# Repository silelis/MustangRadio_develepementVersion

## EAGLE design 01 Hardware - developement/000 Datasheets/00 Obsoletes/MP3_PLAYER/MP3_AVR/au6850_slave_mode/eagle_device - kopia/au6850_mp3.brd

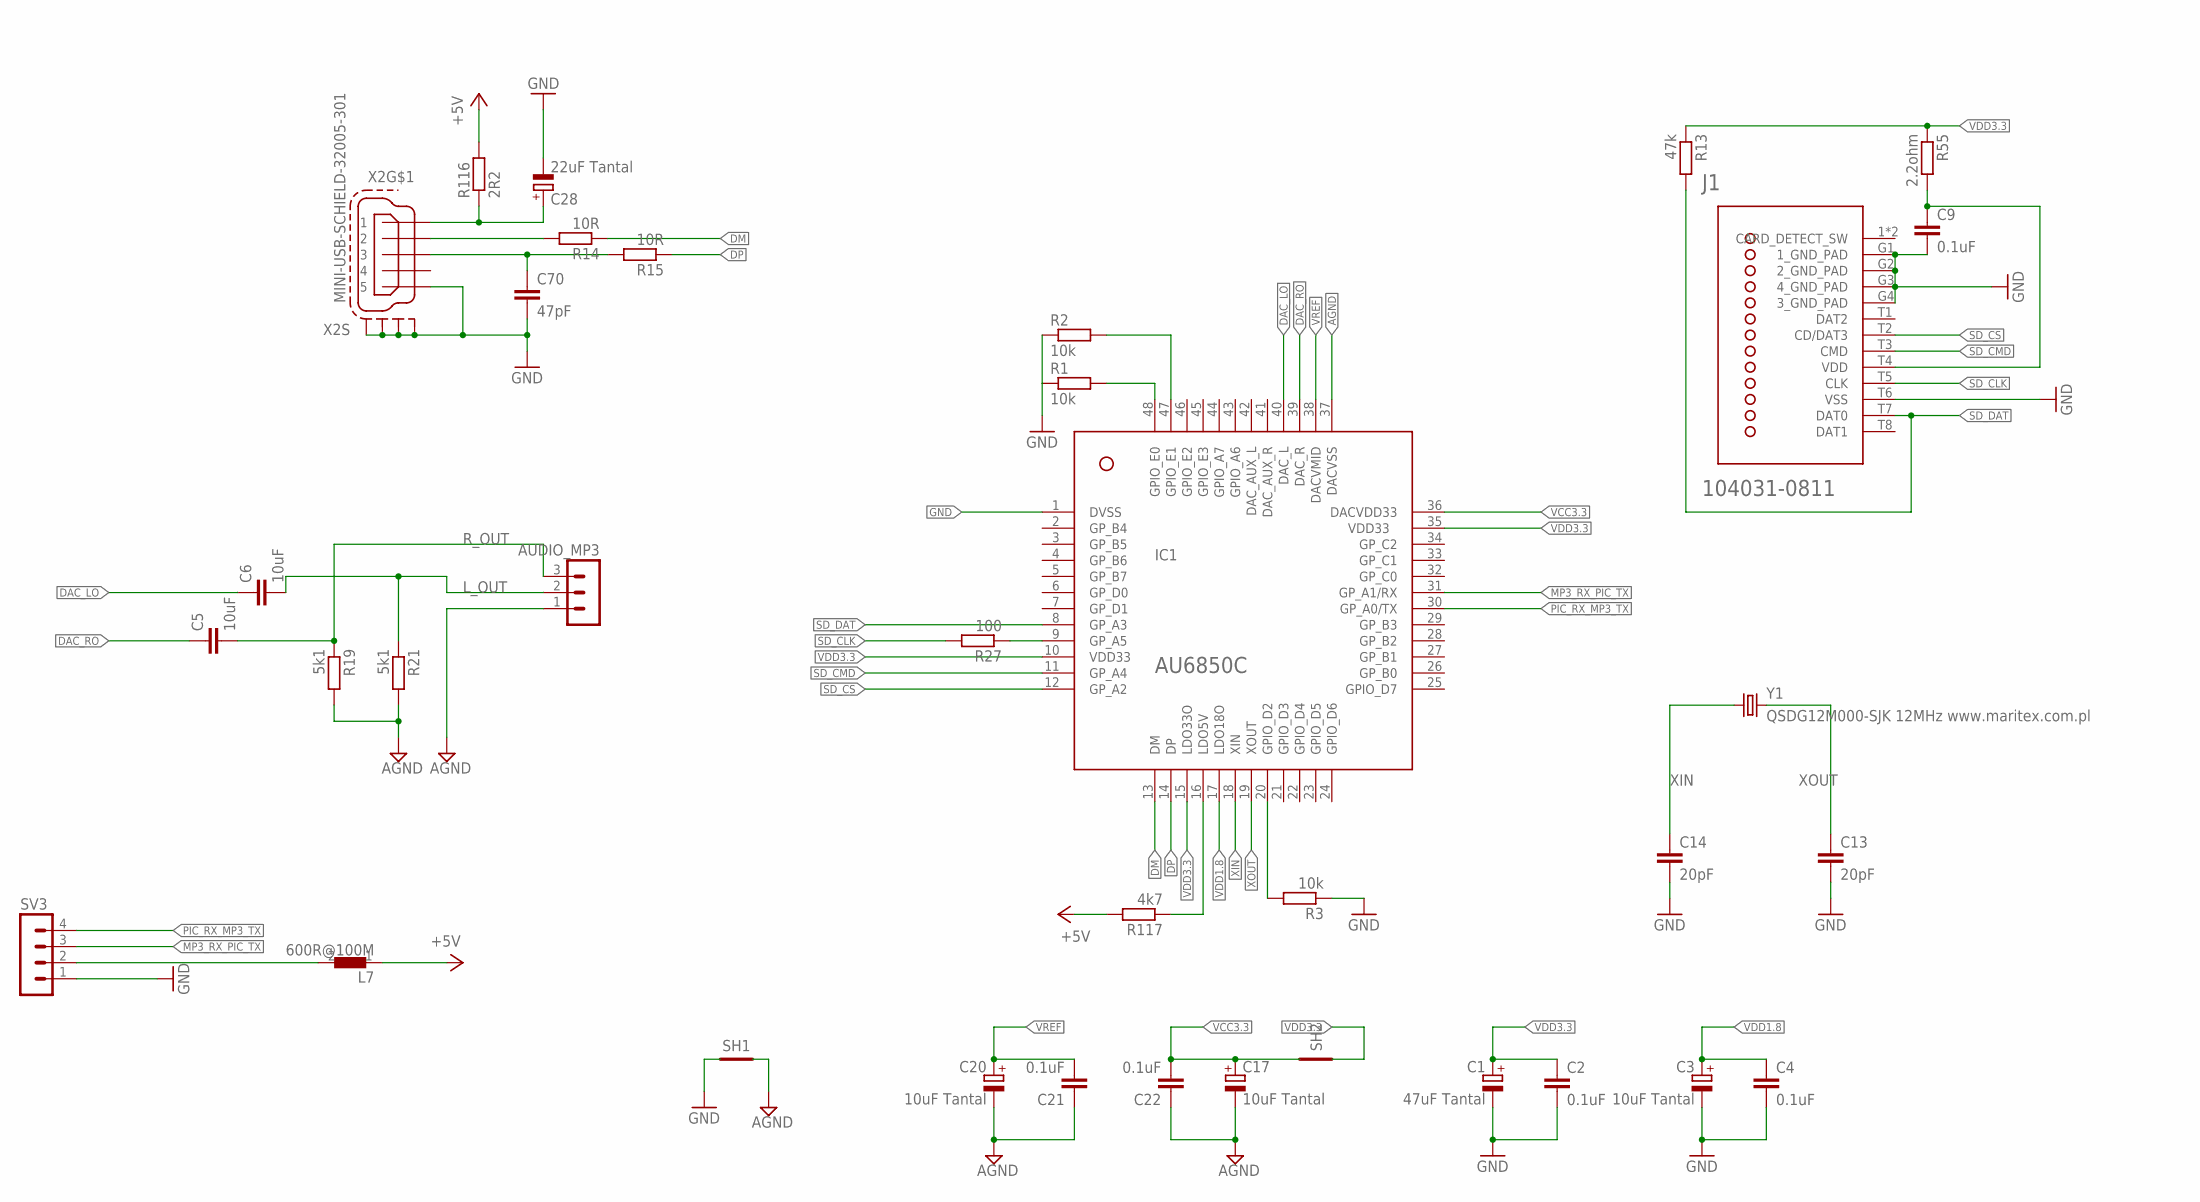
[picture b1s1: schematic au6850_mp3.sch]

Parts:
AUDIO_MP3: MA03-1
C1: 47uF Tantal; B/3528-21R
C2, C4, C9, C21, C22: 0.1uF; C0805
C3, C17, C20: 10uF Tantal; B/3528-21R
C5, C6: 10uF; C0805
C13, C14: 20pF; C0805
C28: 22uF Tantal; SMC_A
C70: 47pF; C0805
IC1: AU6850C; LQFP48-7X7
J1: MOLEX_104031-0811MOLEX_104031-0811_0_0; MOLEX_104031-0811_0
L7: 600R@100M; R0805
R1, R2, R3: 10k; R0805
R13: 47k; R0805
R14, R15: 10R; R0805
R19, R21: 5k1; R0805
R27: 100; R0805
R55: 2.2ohm; R0805
R116: 2R2; R0805
R117: 4k7; R0805
SH1: SHORT-HT5; SHORT_TOP-50
SH2: SHORT-V12_MILS; 12_MILS
SV3: MA04-1
X2: MINI-USB-SCHIELD-32005-301; 32005-301
Y1: QSDG12M000-SJK 12MHz www.maritex.com.pl; CRYSTAL-TXC-7A

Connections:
+5V: L7.1, R116.2, R117.2
AGND: AUDIO_MP3.1, C17.-, C20.-, C21.1, C22.1, IC1.37 (DACVSS), R19.2, R21.2, SH1.2
DAC_LO: C6.1, IC1.40 (DAC_L)
DAC_RO: C5.1, IC1.39 (DAC_R)
DM: IC1.13 (DM), R14.1
DP: IC1.14 (DP), R15.1
GND: C1.-, C2.2, C3.-, C4.2, C9.2, C13.2, C14.2, C28.-, C70.2, IC1.1 (DVSS), J1.G1 (1_GND_PAD), J1.G2 (2_GND_PAD), J1.G3 (4_GND_PAD), J1.G4 (3_GND_PAD), J1.T6 (VSS), R1.1, R2.1, R3.1, SH1.1, SV3.1, X2.5, X2.M1 (S1), X2.M2 (S2), X2.M3 (S3), X2.M4 (S4); also elsewhere on the board
L_OUT: AUDIO_MP3.2, C6.2, R21.1
MP3_RX_PIC_TX: IC1.31 (GP_A1/RX), SV3.3
unnamed: IC1.16 (LDO5V), R117.1
unnamed: IC1.9 (GP_A5), R27.1
unnamed: C28.+, R116.1, X2.1
unnamed: C70.1, R15.2, X2.3
unnamed: R14.2, X2.2
unnamed: L7.2, SV3.2
unnamed 16: C9.1, J1.T4 (VDD), R55.2; also elsewhere on the board
PIC_RX_MP3_TX: IC1.30 (GP_A0/TX), SV3.4
R_OUT: AUDIO_MP3.3, C5.2, R19.1
SD_CLK: J1.T5 (CLK), R27.2; also elsewhere on the board
SD_CMD: IC1.11 (GP_A4), J1.T3 (CMD); also elsewhere on the board
SD_CS: IC1.12 (GP_A2), J1.T2 (CD/DAT3); also elsewhere on the board
SD_DAT: IC1.8 (GP_A3), J1.T7 (DAT0), R13.2; also elsewhere on the board
SLAVE_D2: IC1.20 (GPIO_D2), R3.2
SLAVE_E0: IC1.48 (GPIO_E0), R1.2
SLAVE_E1: IC1.47 (GPIO_E1), R2.2
VCC3.3: C17.+, C22.2, IC1.36 (DACVDD33), SH2.P$2
VDD1.8: C3.+, C4.1, IC1.17 (LDO18O)
VDD3.3: C1.+, C2.1, IC1.10 (VDD33), IC1.15 (LDO33O), IC1.35 (VDD33), R13.1, R55.1, SH2.P$1
VREF: C20.+, C21.2, IC1.38 (DACVMID)
XIN: C14.1, IC1.18 (XIN), Y1.P$1 (1)
XOUT: C13.1, IC1.19 (XOUT), Y1.P$2 (2)

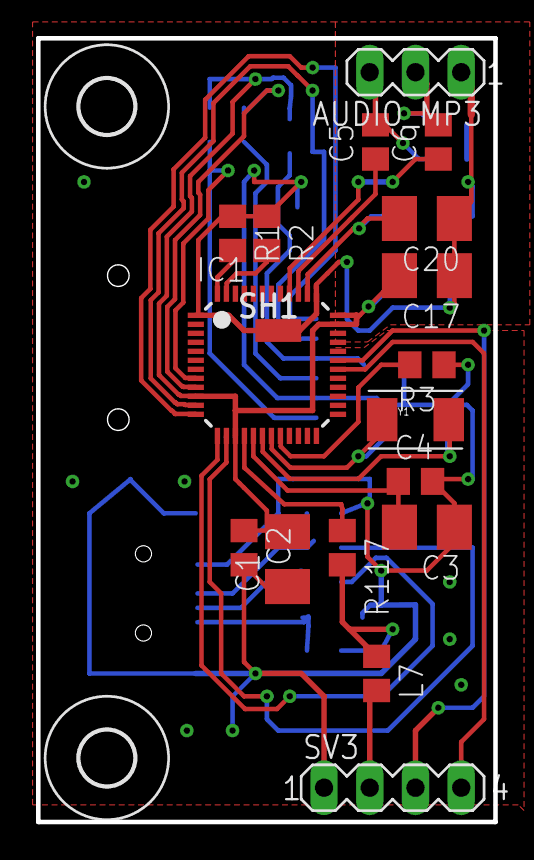
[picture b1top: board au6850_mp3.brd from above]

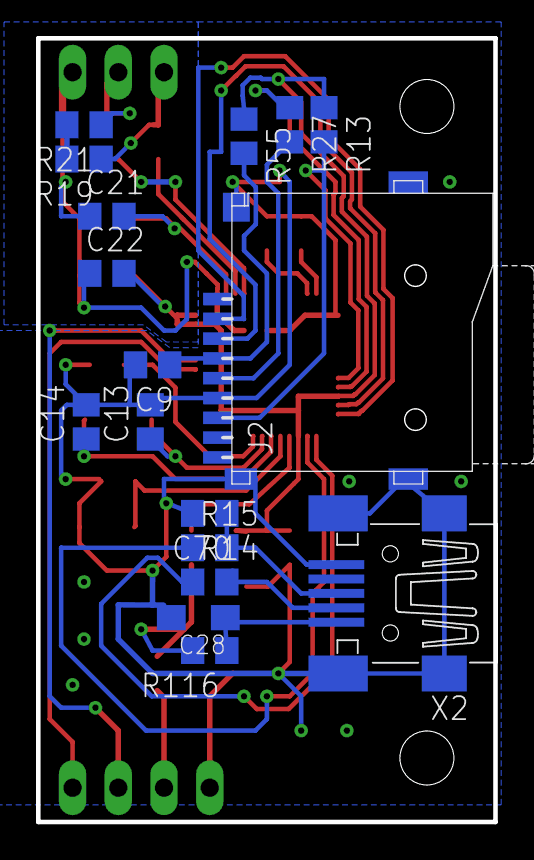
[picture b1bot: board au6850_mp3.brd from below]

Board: 2 copper layers, 25.4 x 43.5 mm, 38 parts (17 on the bottom side), 31 nets.

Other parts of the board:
J2: MICRO_SDMCSP-Q-08-A-SG-T/R; MICRO_SD_8PINS
U$1, U$2: 3,0

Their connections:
GND: J2.P$6, J2.P$SH_1, J2.P$SH_2, J2.P$SH_3, J2.P$SH_4; also elsewhere on the board
unnamed 16: J2.P$4; also elsewhere on the board
SD_CLK: J2.P$5; also elsewhere on the board
SD_CMD: J2.P$3; also elsewhere on the board
SD_CS: J2.P$2; also elsewhere on the board
SD_DAT: J2.P$7; also elsewhere on the board

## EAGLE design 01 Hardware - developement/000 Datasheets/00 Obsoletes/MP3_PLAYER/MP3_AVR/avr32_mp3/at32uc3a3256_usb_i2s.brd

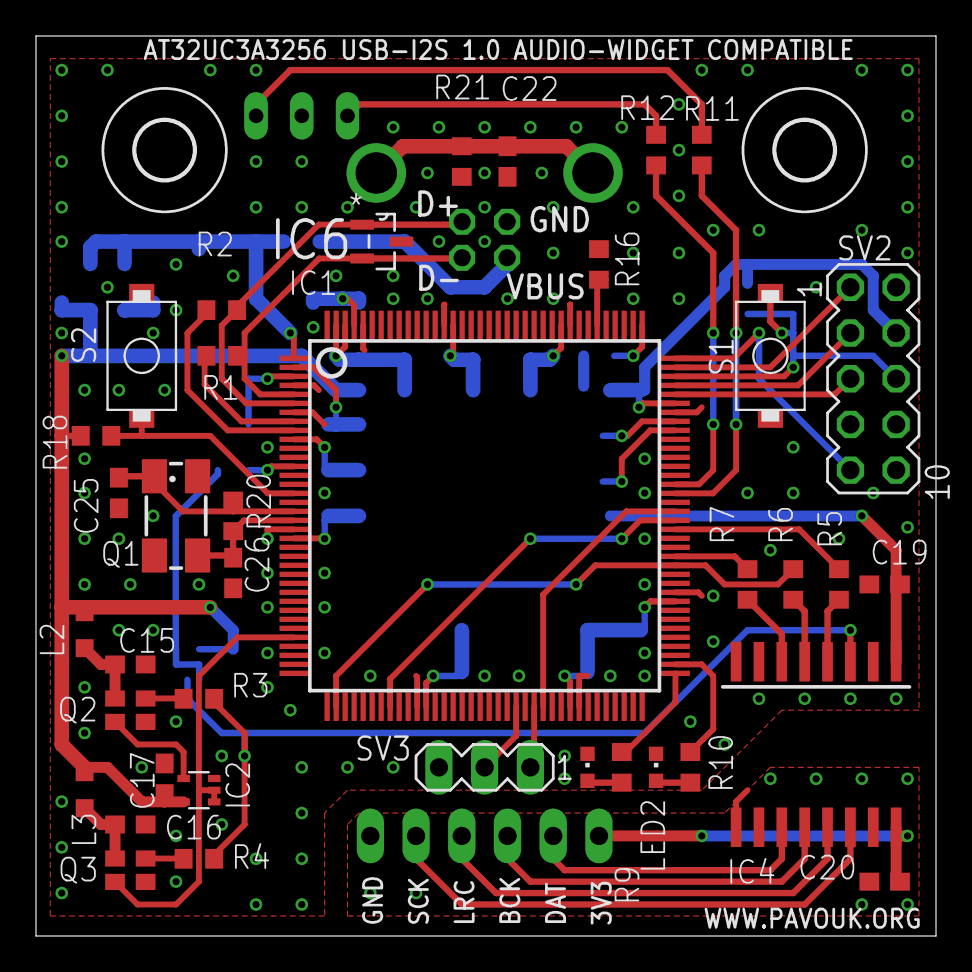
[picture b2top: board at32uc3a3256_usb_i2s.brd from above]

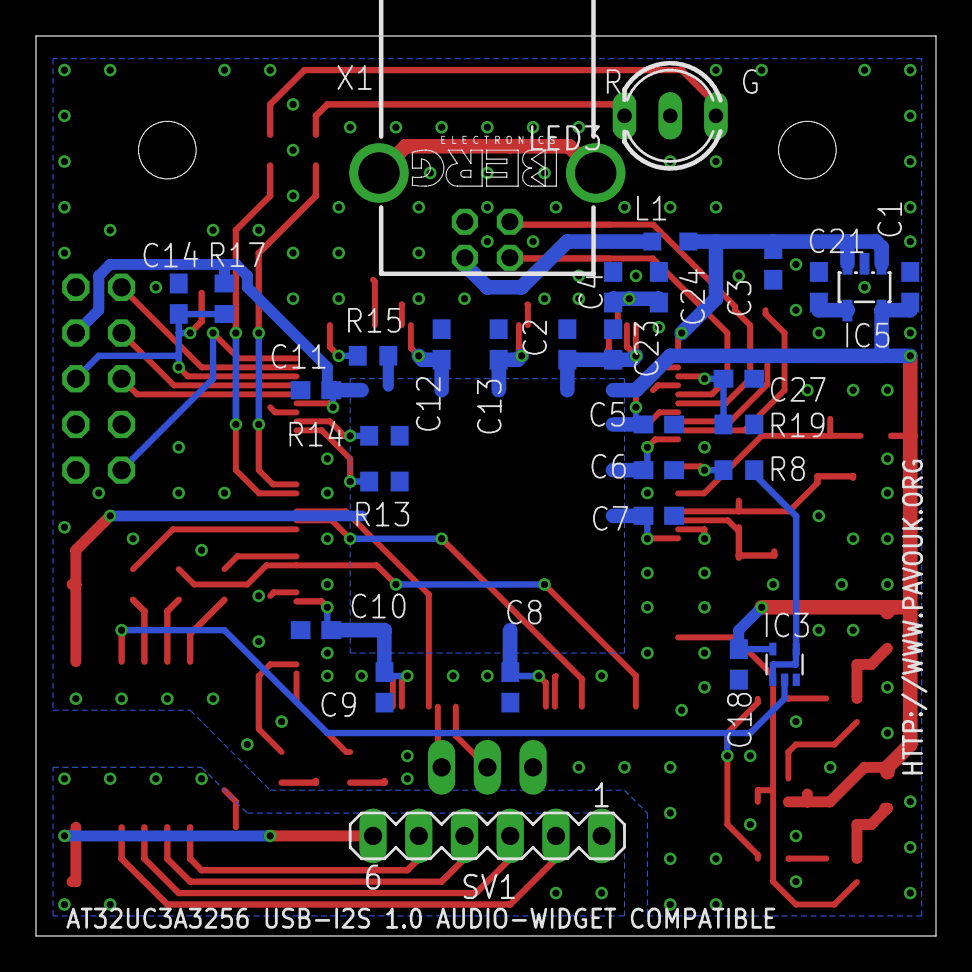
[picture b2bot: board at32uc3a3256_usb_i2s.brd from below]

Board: 2 copper layers, 50.0 x 50.0 mm, 71 parts (31 on the bottom side), 57 nets.

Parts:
C1: 10uF; C0603
C2: 4u7; C0603
C3, C4: 2u2; C0603
C5, C6, C7, C8, C9, C10, C11, C12, C13, C14, C15, C16, C17, C18, C19, C20: 100nF; C0603
C21: 10nF; C0603
C22: 4n7; C0603
C23: 1nF; C0603
C24: 470pF; C0603
C25, C26: 18pF; C0603
C27: 10pF; C0603
H1, H2: MOUNT-HOLE3.2; 3,2
IC1: AT32UC3A3256; LQFP144
IC2: 74LVC1G00DCK; SC70-5
IC3: 74LVC1G80DCK; SC70-5
IC4: ISO7240; SO-16DW
IC5: LP2992-3V3; SOT23-DBV
IC6: TPD2E009DBZR; SOT95P237X112-3N
L1, L2, L3: FB; L2012C
LED1: RED; CHIPLED_0603
LED2: GREEN; CHIPLED_0603
LED3: DUAL 3mm; DUOLED5MM
Q1: 12MHz; CTS406
Q2: 22.5792MHz; CRYSTAL2.5X2
Q3: 24.576MHz; CRYSTAL2.5X2
R1, R2, R3, R4, R5, R6, R7, R8: 39R; R0603
R9, R10, R11, R12: 470; R0603
R13, R14, R15, R16, R17, R18: 4k7; R0603
R19: 6k8; R0603
R20, R21: 1M; R0603
S1: RESET; SWITCH-KSR
S2: PROG; SWITCH-KSR
SV1: MA06-1
SV2: MA05-2
SV3: MA03-1
X1: PN61729-S

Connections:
AD_LRCK: IC1.44, IC1.90
AD_SCLK: IC1.61, IC1.91
DA_LRCK: IC1.89, R5.2
DA_SCLK: IC1.38, IC1.85, R6.2
GND: C1.2, C2.2, C3.2, C4.1, C5.2, C6.2, C7.2, C8.2, C9.1, C10.1, C11.1, C12.1, C13.1, C14.2, C15.1, C16.1, C17.2, C18.2, C19.1, C21.2, C22.2, C23.2, C24.1, C25.2, C26.2, C27.2, IC1.4, IC1.7, IC1.20, IC1.47, IC1.65, IC1.82, IC1.102, IC1.117, IC1.131, IC1.140, IC1.144, IC2.3, IC3.3, IC4.2, IC4.8, IC5.2, IC6.3, LED1.C, LED2.C, LED3.K, Q2.2, Q3.2, R16.1, R19.1, R21.2, S1.1, S2.1, SV2.2, SV2.10, SV3.3, X1.4
GND2: C20.2, IC4.9, IC4.15, SV1.1
GPIO_05_LED2: IC1.94, R12.1
GPIO_08_LED1: IC1.93, R11.1
LRCK: IC4.4, R5.1
MCLK: IC3.2, IC4.3, R3.1, R4.2
MCLK_MCU: IC1.13, R8.1
MCLK_P48_N441: IC1.32, IC2.1, IC2.2, Q3.1
unnamed: C15.2, L2.2, Q2.4
unnamed: IC1.5, IC6.2, R1.1, X1.2
unnamed: Q3.3, R4.1
unnamed: Q2.3, R3.2
unnamed: C16.2, L3.2, Q3.4
unnamed: IC1.6, IC6.1, R2.1, X1.3
unnamed: IC1.8, R1.2
unnamed: C26.1, IC1.19, Q1.3, R20.2
unnamed: C25.1, IC1.18, Q1.1, R20.1
unnamed: IC1.9, R2.2
unnamed: C4.2, C24.2, IC1.141
unnamed: IC1.108, SV2.9
unnamed: IC1.114, R16.2
unnamed: C22.1, R21.1, X1.S1, X1.S2
unnamed: C27.1, IC1.3, R19.2
unnamed: C20.1, IC4.16, SV1.6
unnamed: IC4.14, SV1.2
unnamed: IC4.13, SV1.3
unnamed: IC4.12, SV1.4
unnamed: LED1.A, R9.2
unnamed: LED2.A, R10.2
unnamed: IC1.74, R10.1
unnamed: IC1.73, R9.1
unnamed: IC1.109, R15.2
unnamed: IC1.101, R14.1
unnamed: IC1.100, R13.1
unnamed: IC4.11, SV1.5
unnamed: IC4.5, R6.1
unnamed: IC1.86, R7.2
unnamed: IC4.6, R7.1
unnamed: IC3.1, IC3.4, R8.2
unnamed: L1.1, X1.1
unnamed: LED3.AG, R11.2
unnamed: C21.1, IC5.4
unnamed: LED3.AR, R12.2
unnamed: IC2.4, Q2.1
NSRST: C14.1, IC1.106, R17.1, S1.2, SV2.6
PROG: IC1.16, R18.2, S2.2
TCK: IC1.107, SV2.1
TDO: IC1.105, SV2.3
TMS: IC1.104, SV2.5
UART_RX: IC1.60, SV3.1
UART_TX: IC1.58, SV3.2
VBUS: C3.1, IC1.1, IC5.1, IC5.3, L1.2
VCC: C1.1, C2.1, C5.1, C6.1, C7.1, C8.1, C9.2, C10.2, C11.2, C12.2, C13.2, C17.1, C18.1, C19.2, C23.1, IC1.2, IC1.10, IC1.21, IC1.48, IC1.64, IC1.81, IC1.103, IC1.118, IC1.130, IC1.142, IC1.143, IC2.5, IC3.5, IC4.1, IC5.5, L2.1, L3.1, R13.2, R14.2, R15.1, R17.2, R18.1, SV2.4

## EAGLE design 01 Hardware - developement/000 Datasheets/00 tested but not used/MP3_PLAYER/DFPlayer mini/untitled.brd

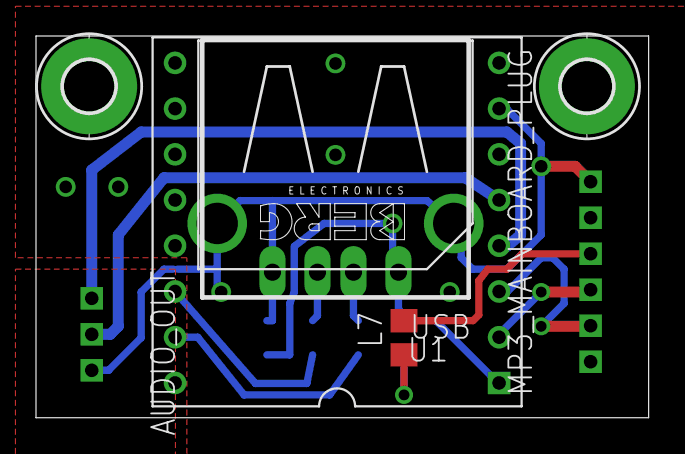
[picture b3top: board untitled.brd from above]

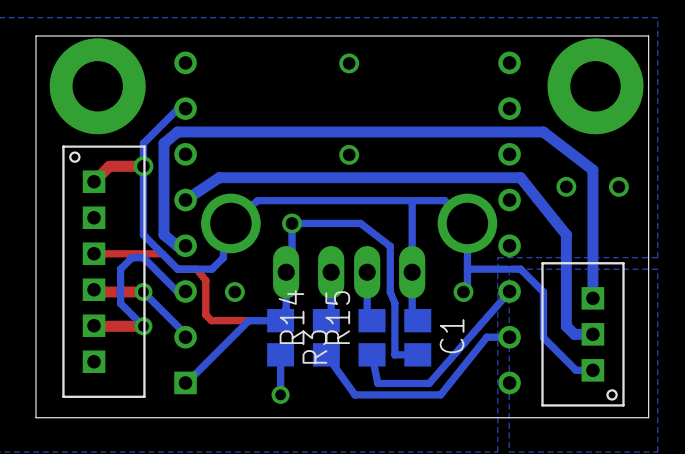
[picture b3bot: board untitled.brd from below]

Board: 2 copper layers, 34.0 x 21.2 mm, 12 parts (5 on the bottom side), 13 nets.

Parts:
AUDIO_OUT: JST_3_PIN_B3B-PH-KS; B3B-PH-KS
C1: 100n; C0805
H1, H2: MOUNT-PAD-ROUND2.8; 2,8-PAD
L7: 600R@100M; R0805
MP3_MAINBOARD_PLUG: JST_6_PIN_B6B-PH-KS; B6B-PH-KS
R3: R10 805; R0805
R14, R15: 10R; R0805
SH1: SHORT-V12_MILS; 12_MILS
U1: DFPLAYER_MINI_MP3_TF_16P; 20_5M_SQUARE
USB: PN87520-S

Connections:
+5V: C1.2, R3.1, U1.P$1, USB.1
AGND: AUDIO_OUT.P$1, SH1.P$2
DM: R14.1, U1.P$15
DP: R15.1, U1.P$14
GND: C1.1, MP3_MAINBOARD_PLUG.P$1, SH1.P$1, U1.P$7, U1.P$10, USB.4, USB.S1, USB.S2
unnamed: AUDIO_OUT.P$3, U1.P$4
unnamed: AUDIO_OUT.P$2, U1.P$5
unnamed: L7.2, MP3_MAINBOARD_PLUG.P$3
unnamed: MP3_MAINBOARD_PLUG.P$4, U1.P$2
unnamed: MP3_MAINBOARD_PLUG.P$5, U1.P$3
unnamed: R15.2, USB.3
unnamed: R14.2, USB.2
unnamed: L7.1, R3.2

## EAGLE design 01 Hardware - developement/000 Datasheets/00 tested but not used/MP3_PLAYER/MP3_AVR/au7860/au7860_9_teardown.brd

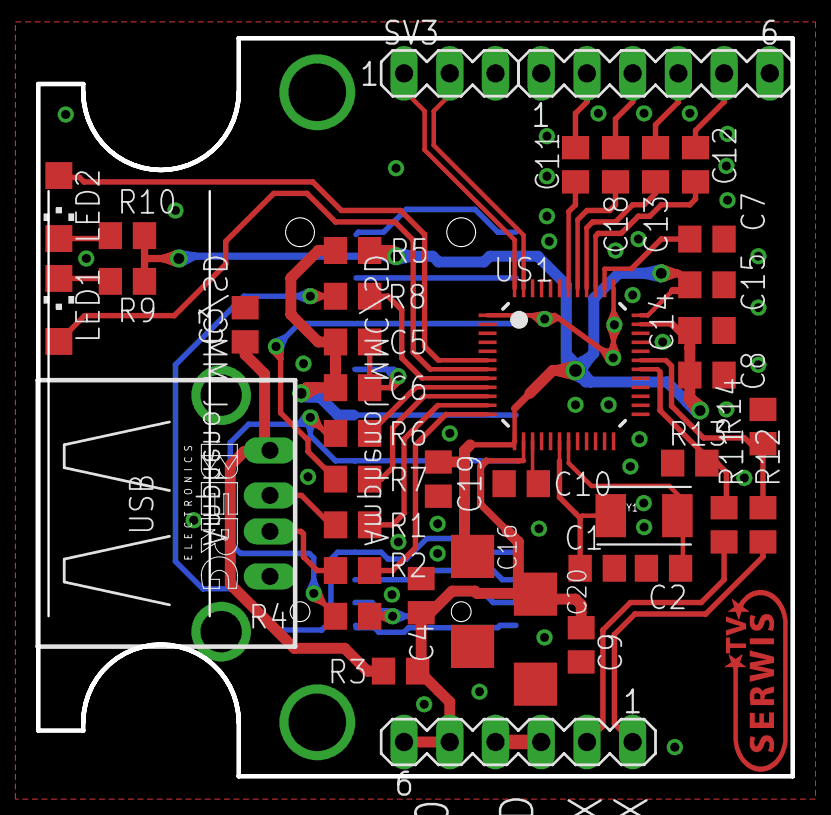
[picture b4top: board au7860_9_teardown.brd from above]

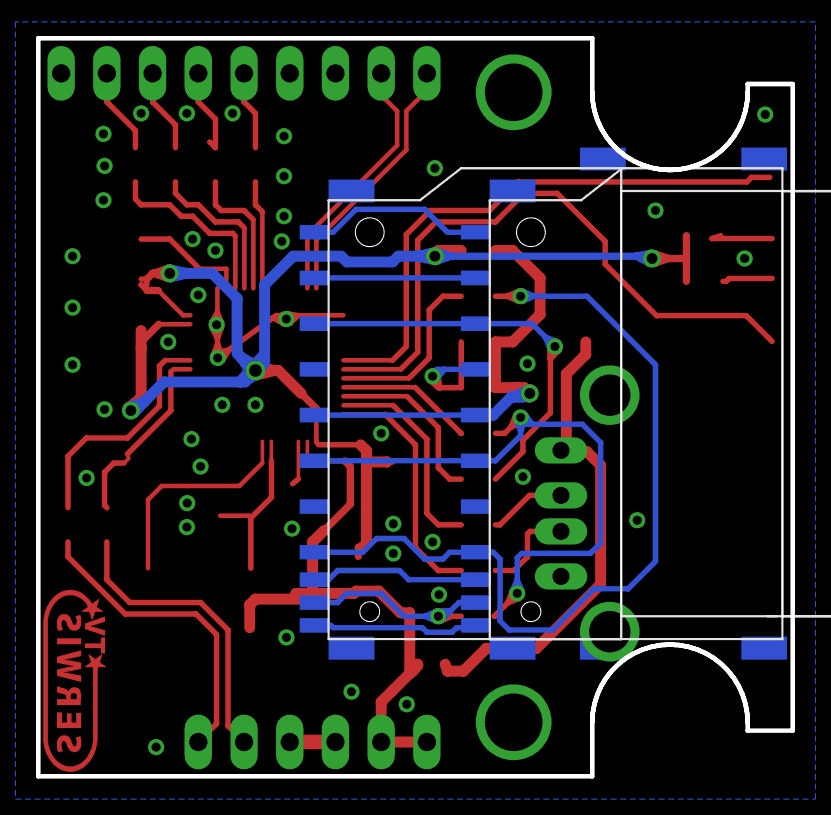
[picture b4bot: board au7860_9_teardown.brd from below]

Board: 2 copper layers, 41.9 x 41.0 mm, 43 parts (2 on the bottom side), 42 nets.

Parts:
C1, C2: 22p; C0805
C3, C4, C5, C6, C7, C8, C9, C10, C11, C12, C13, C14, C15, C18, C19: 10u; C0805
C16, C20: 100u/6V niobowy; SMC_C
LED1: Zielona; CHIPLED_1206
LED2: Czerwona; CHIPLED_1206
R1, R2, R6, R7, R8: 100; R0805
R3, R5, R11, R12: 1; R0805
R4: 10k; R0805
R9, R10: 470; R0805
R13, R14: nie montowac; R0805
SV1, SV2: Nie montowac; MA06-1
SV3: MA03-1
U$1, U$2: Nie montować; SDCMF-10915W010
US1: AU7860; LQFP48-7X7
USB: Nie montowac; PN87520-S
Y1: QSDG12M000-SJK 12MHz www.maritex.com.pl; CRYSTAL-TXC-7A

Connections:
+3V3: C8.1, C14.1, C15.1, C16.+, C19.1, R5.2, R9.2, R10.2, US1.13, US1.35, US1.36
+5V: C4.1, C9.1, C20.+, R3.2, SV2.5, SV2.6, US1.14
GND: C1.1, C2.1, C3.2, C4.2, C5.2, C6.2, C7.2, C8.2, C9.2, C10.2, C14.2, C15.2, C16.-, C19.2, C20.-, R13.1, R14.2, SV1.1, SV1.6, SV2.3, SV2.4, SV3.3, U$1.3, U$1.6, U$1.12, U$1.13, U$1.14, U$1.15, U$2.3, U$2.6, U$2.12, U$2.13, U$2.14, U$2.15, US1.1, US1.37, USB.4, USB.S1, USB.S2
unnamed: C1.2, US1.18, Y1.P$2
unnamed: C2.2, US1.19, Y1.P$1
unnamed: R7.1, U$1.2, U$2.2
unnamed: C13.2, US1.40
unnamed: C12.2, US1.39
unnamed: LED2.C, R10.1
unnamed: LED1.C, R9.1
unnamed: C7.1, US1.38
unnamed: C13.1, SV1.4
unnamed: C10.1, US1.15
unnamed: C12.1, SV1.5
unnamed: R4.1, U$1.11, U$2.11
unnamed: R4.2, R6.1, U$1.5, U$2.5
unnamed: R8.1, U$1.7, U$2.7
unnamed: R11.1, SV2.2
unnamed: C5.1, C6.1, R5.1, U$1.4, U$2.4
unnamed: C18.2, US1.41
unnamed: R11.2, R13.2, US1.30
unnamed: R8.2, US1.8
unnamed: R7.2, US1.10
unnamed: R6.2, US1.9
unnamed: R12.1, SV2.1
unnamed: C3.1, R3.1, USB.1
unnamed: R1.1, USB.2
unnamed: R2.1, USB.3
unnamed: R12.2, R14.1, US1.31
unnamed: R1.2, US1.11
unnamed: R2.2, US1.12
unnamed: SV3.2, US1.47
unnamed: SV3.1, US1.48
unnamed: C11.2, US1.42
unnamed: C11.1, SV1.2
unnamed: C18.1, SV1.3
unnamed: LED2.A, US1.6
unnamed: LED1.A, US1.7
unnamed: U$1.8, U$2.8
unnamed: U$1.9, U$2.9
unnamed: U$1.1, U$2.1
unnamed: U$1.10, U$2.10

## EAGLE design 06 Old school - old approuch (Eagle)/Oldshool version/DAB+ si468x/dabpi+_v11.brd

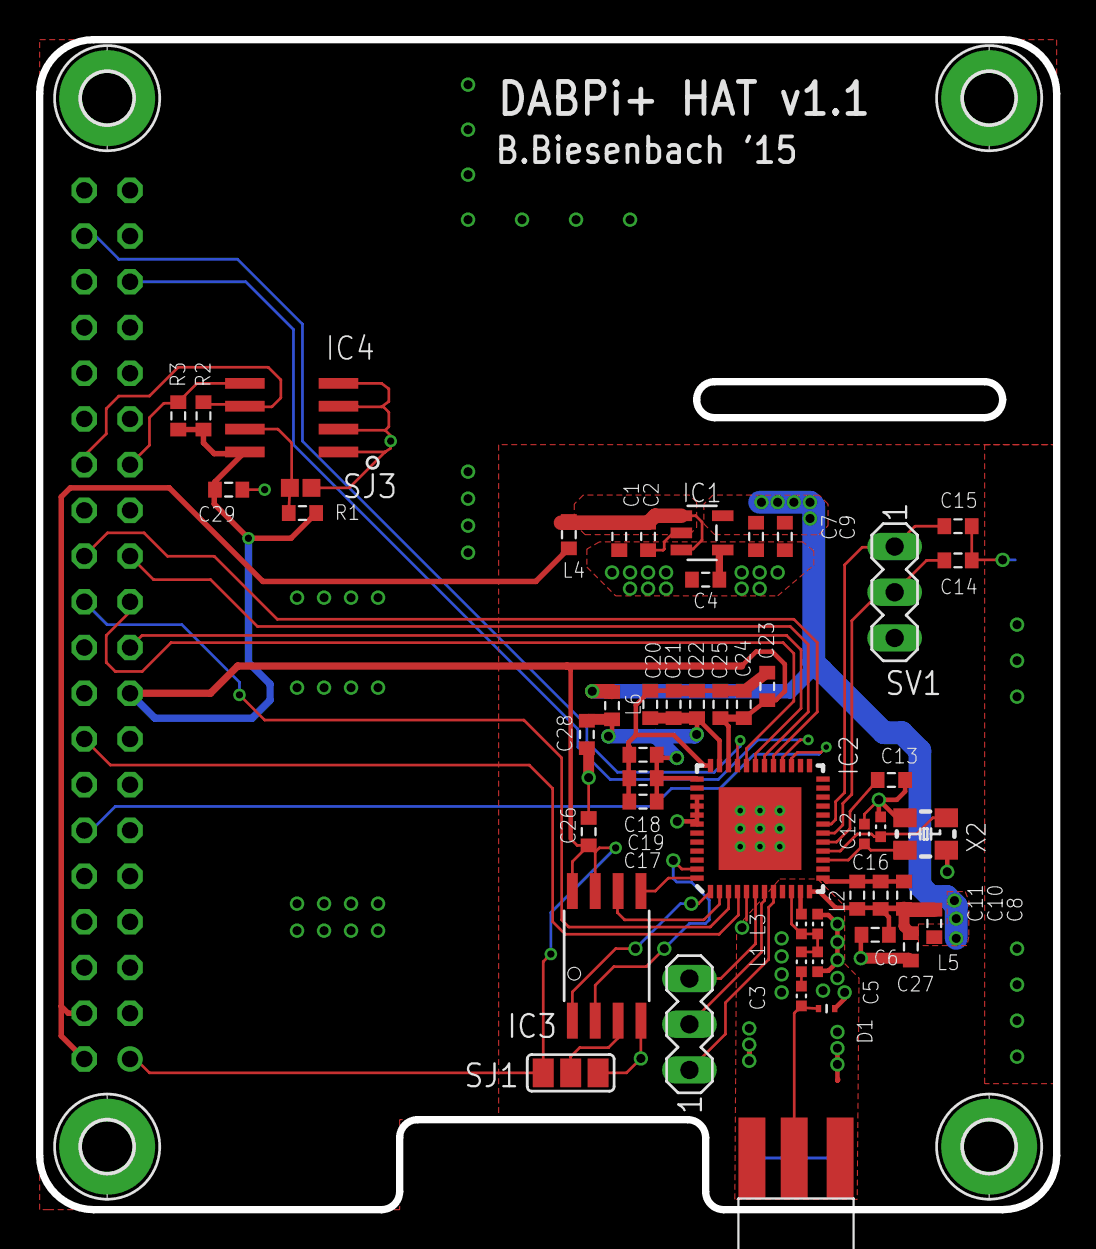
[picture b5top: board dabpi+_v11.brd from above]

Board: 2 copper layers, 56.5 x 65.0 mm, 54 parts (1 on the bottom side), 39 nets.

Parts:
C1, C8, C13, C17, C20, C23, C28: 1u; SMD0603
C2, C7, C27, C29: 100n; SMD0603
C3: 33p; SMD0402
C4: 10n; SMD0603
C5: 2.7p; SMD0402
C6, C11, C14, C15, C19, C22, C25: 8.2p; SMD0603
C9: 10u; SMD0603
C10, C18, C21, C24, C26: 2.2n; SMD0603
C12, C16: n.b.; SMD0402
D1: ESD9L5.0; SOD923
H1, H2, H3, H4: MOUNT-PAD-ROUND2.8; 2,8-PAD
IC1: TPS79318DBVR; SOT23-5
IC2: SI4688-A10-GM; QFN48
IC3: SST25VF016B; SO08
IC4: 24LC32ASN; SO-08
L1: 18nH; SMD0402
L2: 120nH; SMD0402
L3: 22nH; SMD0402
L4, L5, L6: 0R; SMD0603
R1, R2, R3: 3.9k; SMD0603
SJ1: SJ_2
SJ3: SJ
SV1, SV4: MA03-1
SV5: FE20-2
X1: SMA_LP_1.57MM
X2: 19.2MHz; XTAL_3.2X2.5

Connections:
+1V8: C7.1, C9.1, IC1.5, L5.1, L6.1
+3V3: C23.1, C24.1, C25.1, C26.1, C29.1, IC2.34, IC3.7, IC3.8, IC4.8, R1.2, R2.2, R3.2, SJ1.3, SV5.1, SV5.17
+5V: L4.1, SV5.2, SV5.4
FLASH_CE: IC2.1, IC3.1
FLASH_SCK: IC2.2, IC3.6
FLASH_SI: IC2.48, IC3.5
FLASH_SO: IC2.47, IC3.2
GND: C1.2, C2.2, C4.2, C5.1, C6.2, C7.2, C9.2, C12.1, C13.2, C14.2, C15.2, C16.1, C26.2, C27.2, C28.2, C29.2, D1.A, IC1.2, IC2.5, IC2.9, IC2.39, IC2.40, IC2.41, IC2.42, IC2.EP, IC3.4, IC4.1, IC4.2, IC4.3, IC4.4, L2.1, SJ1.1, SJ3.1, SV1.3, SV5.6, SV5.9, SV5.14, SV5.20, SV5.25, SV5.30, SV5.34, SV5.39, X1.GND, X1.GND@1, X1.GND@2, X1.GND@3, X2.2, X2.4
ID_SC: IC4.6, R2.1, SV5.28
ID_SD: IC4.5, R3.1, SV5.27
INT: IC2.3, SV5.22
LDO_IN: C1.1, C2.1, IC1.1, IC1.3, L4.2
unnamed: C3.2, L1.1
unnamed: C5.2, IC2.10, L1.2, L2.2, L3.2
unnamed: IC2.11, L3.1
unnamed: C8.2, C10.2, C11.2, IC2.13
unnamed: C17.2, C18.2, C19.2, C20.2, C21.2, C22.2, C23.2, C24.2, C25.2, IC2.36
unnamed: C12.2, IC2.15, X2.1
unnamed: C16.2, IC2.16, X2.3
unnamed: C13.1, IC2.17
unnamed: IC3.3, SJ1.2
unnamed: C4.1, IC1.4
unnamed: C6.1, C8.1, C10.1, C11.1, C27.1, IC2.12, L5.2
unnamed: IC2.6, SV4.3
unnamed: C17.1, C18.1, C19.1, C20.1, C21.1, C22.1, C28.1, IC2.35, IC2.37, L6.2
unnamed: IC2.7, SV4.2
unnamed: IC2.8, SV4.1
unnamed: IC4.7, R1.1, SJ3.2
PCM_CLK: IC2.27, SV5.12
PCM_DIN: IC2.33, SV5.38
PCM_FS: IC2.28, SV5.35
RF_IN: C3.1, D1.K, X1.PIN
SI4688_LOUT: C14.1, IC2.18, SV1.2
SI4688_ROUT: C15.1, IC2.19, SV1.1
SI4688_RSTB: IC2.4, SV5.16
SPI0_CE0_N: IC2.29, SV5.24
SPI0_MISO: IC2.32, SV5.21
SPI0_MOSI: IC2.31, SV5.19
SPI0_SCLK: IC2.30, SV5.23

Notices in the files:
parts and their libraries:
SparkFun-FreqCtrl: Licensing: Creative Commons ShareAlike 4.0 International - https://creativecommons.org/licenses/by-sa/4.0
SparkFun-FreqCtrl: Licensing: CC v3.0 Share-Alike You are welcome to use this library for commercial purposes.
